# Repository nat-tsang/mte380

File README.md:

# Welcome to MTE380: PiDdy
We're a team of 5 students from the University of Waterloo tasked with creating a search and rescue robot to complete a course, via line following with computer vision, pick up a lego man and drop off the lego man in a safe zone. 

The course consists of a 6x6 grid of 30cm x 30cm squares, with a red tape path guiding the robot from the starting point to the target. A green tape box outlines two safe zones which the Lego man can be dropped off in. 

On game day, our robot was able to achieve times of 15 seconds on the first two runs, and 13 seconds in the third run. In total it weighed 131 g, mostly thanks to the mechanical and electrical design of the robot. The robot's software architecutre consisted of a Teensy MCU running the main control logic, and a Pixy camera module for the perception. 
# Software

This repo contains all of the software behind our robot, PiDdy. It specifically contains the PD controller for line following, the main state machine for feature arbitration between line following, picking up the lego man and dropping off the lego man.

## Code Standards

We are following OOP coding practices for clean, reusable code.

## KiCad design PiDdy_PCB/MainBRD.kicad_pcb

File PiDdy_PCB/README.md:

Space for all things to do custom pcb (PiDdy's chassis)

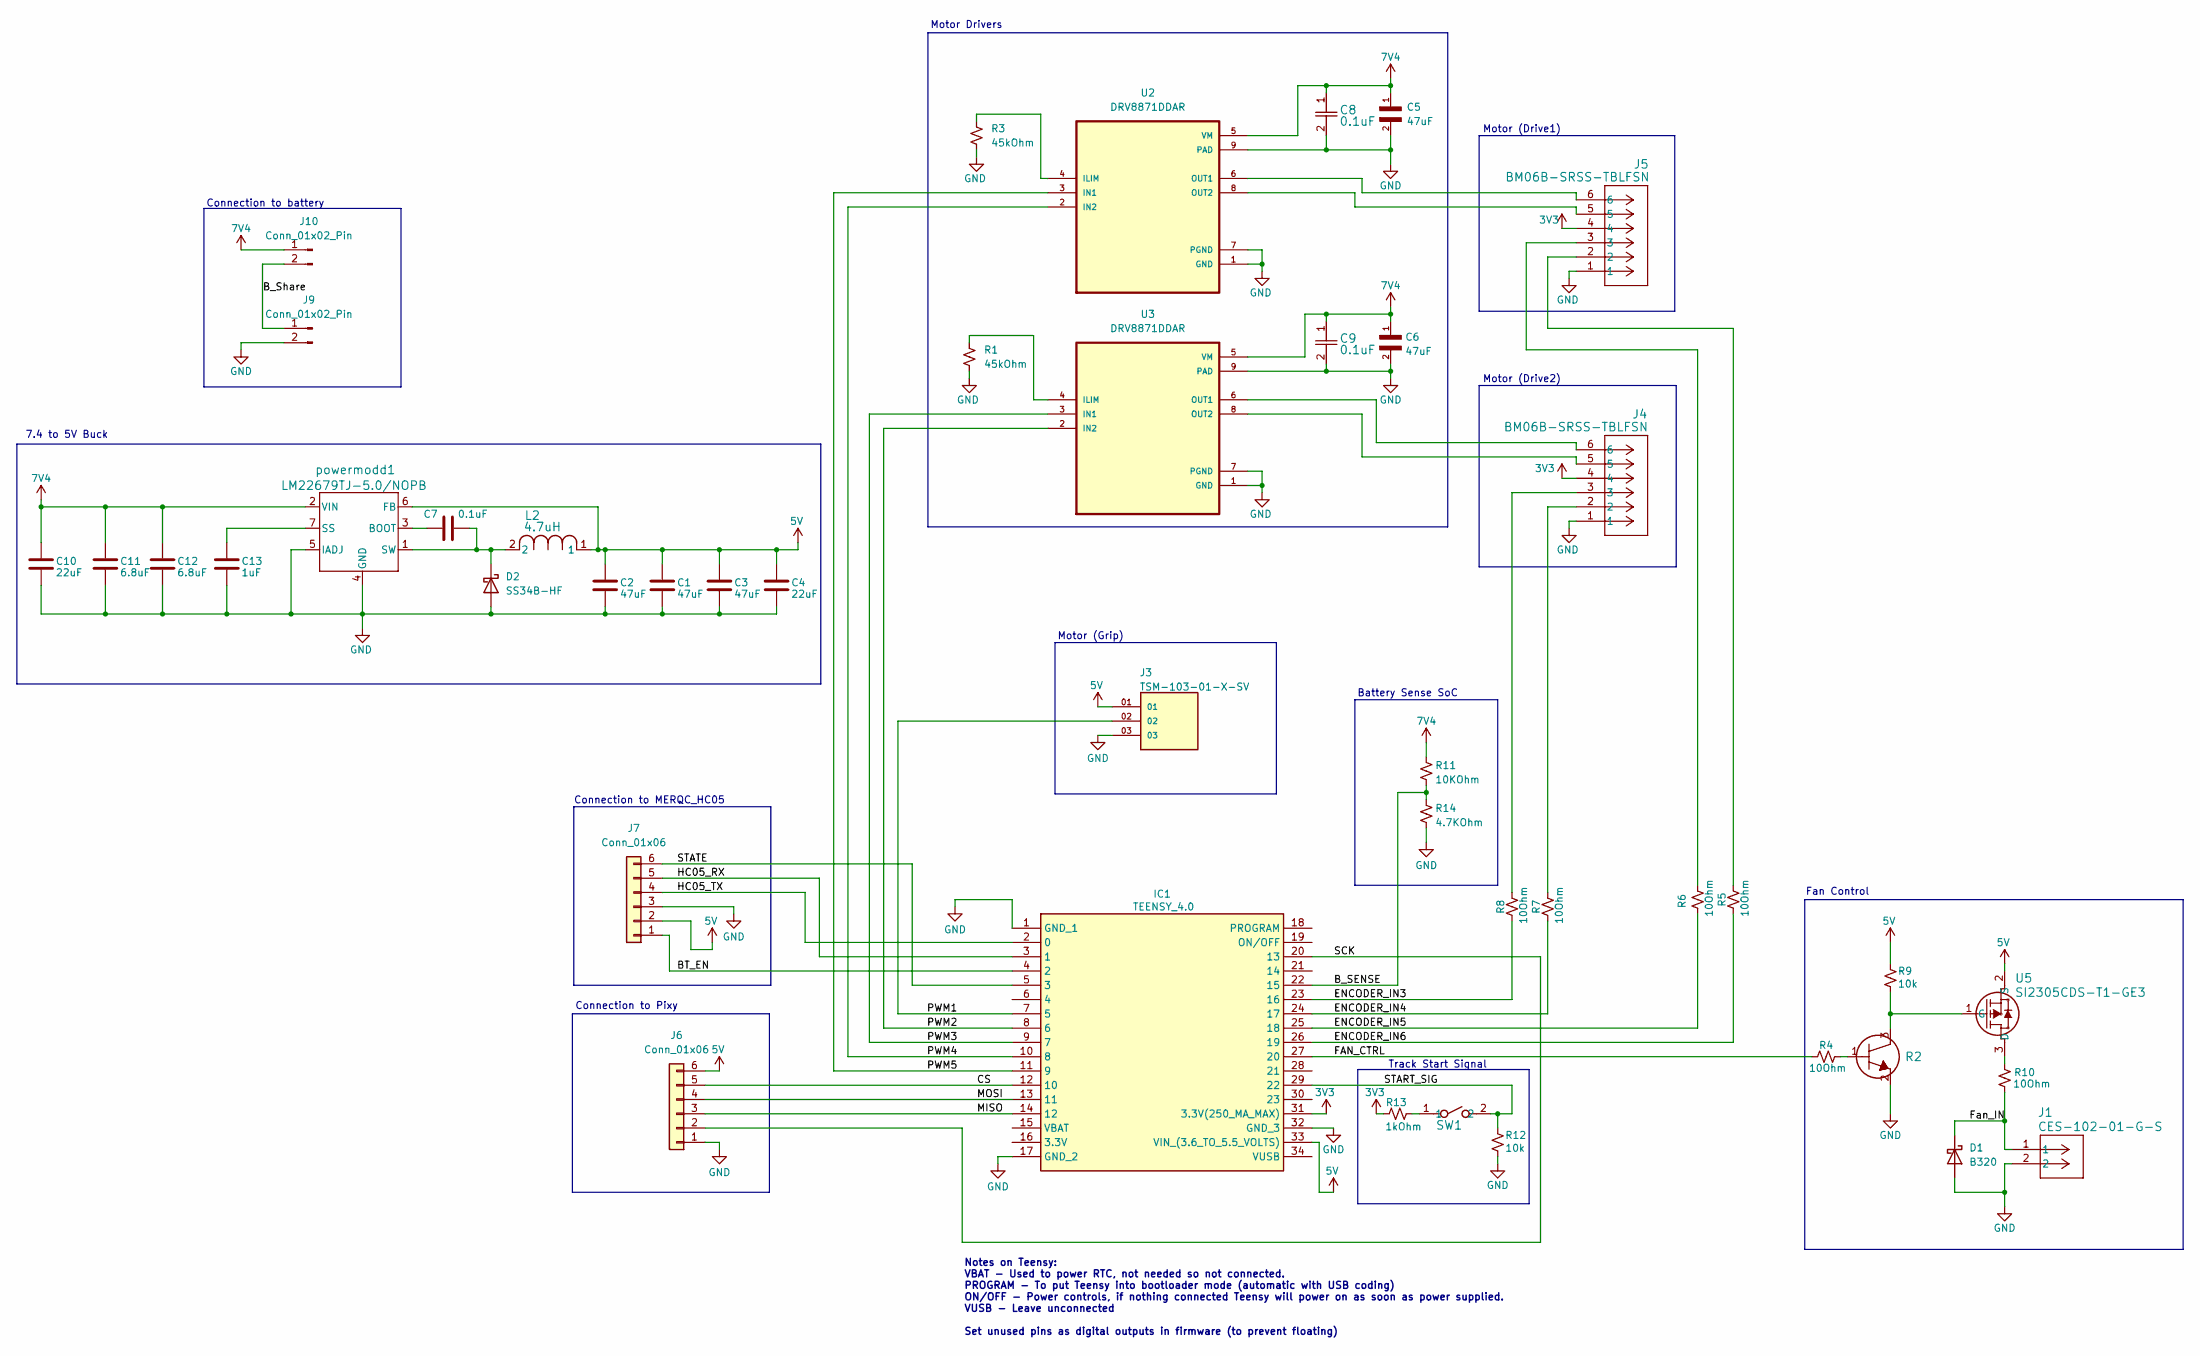
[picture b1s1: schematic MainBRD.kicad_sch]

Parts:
C1, C2, C3, C5, C6: 47uF; C_1210_3225Metric_Pad1.33x2.70mm_HandSolder
C4, C10: 22uF; C_1206_3216Metric_Pad1.33x1.80mm_HandSolder
C7: 0.1uF; C_0402_1005Metric_Pad0.74x0.62mm_HandSolder
C8, C9: 0.1uF; C_0402_1005Metric
C11: 6.8uF; LED_0805_2012Metric_Pad1.15x1.40mm_HandSolder
C12: 6.8uF; C_0805_2012Metric_Pad1.18x1.45mm_HandSolder
C13: 1uF; C_0402_1005Metric_Pad0.74x0.62mm_HandSolder
D1: B320; D_SMC
D2: SS34B-HF; SS34B
IC1: TEENSY_4.0; TEENSY40; Manufacturer_Part_Number TEENSY 4.0
J1: CES-102-01-G-S; CON2_1X2_TU_SLW_SAI
J3: TSM-103-01-X-SV; SAMTEC_TSM-103-01-X-SV; PARTREV D
J4, J5: BM06B-SRSS-TBLFSN; CONN_BM06B-SRSS-TB_JST
J6, J7: Conn_01x06; PinHeader_1x06_P2.54mm_Vertical
J9, J10: Conn_01x02_Pin; PinHeader_1x02_P2.54mm_Vertical
L2: 4.7uH; IND_VLS5045EX-4R7M
R1, R3: 45kOhm; RES_ERJ3EKF4532V
R2: 2SC5663T2L; TRANS_2SC5658T2_ROM
R4, R5, R6, R7, R8, R10: 10Ohm; ERJ_2RKF10R0X
R9, R12: 10k; RES_ERJ2RKF4702X
R11: 10KOhm; R_1206_3216Metric
R13: 1kOhm; ERJ_2RKF10R0X
R14: 4.7KOhm; R_1206_3216Metric
SW1: PTS636 SM50J SMTR LFS; SW_PTS636_CNK
U2, U3: DRV8871DDAR; lili_foot
U5: SI2305CDS-T1-GE3; TO-236_VIS
powermodd1: LM22679TJ-5.0/NOPB; LM22679TJ

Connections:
3V3: IC1.31 (3.3V(250_MA_MAX)), J4.4, J5.4, R13.2
5V: C1.1, C2.1, C3.1, C4.1, IC1.33 (VIN_(3.6_TO_5.5_VOLTS)), J3.01, J6.6, J7.2, L2.1, R9.1, U5.2 (S), powermodd1.6 (FB)
7V4: C5.1, C6.1, C8.1, C9.1, C10.1, C11.1, C12.1, J10.1, R11.1, U2.5 (VM), U3.5 (VM), powermodd1.2 (VIN)
/BT_EN: IC1.4 (2), J7.1
/B_SENSE: IC1.22 (15), R11.2, R14.1
/B_Share: J9.1, J10.2
/CS: IC1.12 (10), J6.5
/ENCODER_IN3: IC1.23 (16), R8.2
/ENCODER_IN4: IC1.24 (17), R7.2
/ENCODER_IN5: IC1.25 (18), R6.2
/ENCODER_IN6: IC1.26 (19), R5.2
/FAN_CTRL: IC1.27 (20), R4.2
/Fan_IN: D1.1 (K), J1.1, R10.2
/HC05_RX: IC1.3 (1), J7.5
/HC05_TX: IC1.2 (0), J7.4
/MISO: IC1.14 (12), J6.3
/MOSI: IC1.13 (11), J6.4
/PWM1: IC1.7 (5), J3.02
/PWM2: IC1.8 (6), U3.2 (IN2)
/PWM3: IC1.9 (7), U3.3 (IN1)
/PWM4: IC1.10 (8), U2.2 (IN2)
/PWM5: IC1.11 (9), U2.3 (IN1)
/SCK: IC1.20 (13), J6.2
/START_SIG: IC1.29 (22), R12.1, SW1.2
/STATE: IC1.5 (3), J7.6
GND: C1.2, C2.2, C3.2, C4.2, C5.2, C6.2, C8.2, C9.2, C10.2, C11.2, C12.2, C13.2, D1.2 (A), D2.2 (A), IC1.1 (GND_1), IC1.17 (GND_2), IC1.32 (GND_3), J1.2, J3.03, J4.1, J5.1, J6.1, J7.3, J9.2, R1.1, R2.2 (EMITTER), R3.1, R12.2, R14.2, U2.1 (GND), U2.7 (PGND), U2.9 (PAD), U3.1 (GND), U3.7 (PGND), U3.9 (PAD), powermodd1.4 (GND), powermodd1.5 (IADJ)
unnamed: C7.2, D2.1 (K), L2.2, powermodd1.1 (SW)
unnamed: J4.2, R7.1
unnamed: J4.3, R8.1
unnamed: J5.2, R5.1
unnamed: J5.3, R6.1
unnamed: R2.1 (Base), R4.1
unnamed: R2.3 (Collector), R9.2, U5.1 (G)
unnamed: R13.1, SW1.1
unnamed: R3.2, U2.4 (ILIM)
unnamed: J5.6, U2.6 (OUT1)
unnamed: J5.5, U2.8 (OUT2)
unnamed: R1.2, U3.4 (ILIM)
unnamed: J4.6, U3.6 (OUT1)
unnamed: J4.5, U3.8 (OUT2)
unnamed: R10.1, U5.3 (D)
unnamed: C7.1, powermodd1.3 (BOOT)
unnamed: C13.1, powermodd1.7 (SS)

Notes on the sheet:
Motor (Grip)
Motor (Drive1)
Connection to Pixy
Motor (Drive2)
Track Start Signal
Motor Drivers
Connection to battery
Notes on Teensy: VBAT - Used to power RTC, not needed so not connected. PROGRAM - To put Teensy into bootloader mode (automatic with USB coding) ON/OFF - Power controls, if nothing connected Teensy will power on as soon as power supplied. VUSB - Leave unconnected Set unused pins as digital outputs 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
Battery Sense SoC
Connection to MERQC_HC05
Fan Control
7.4 to 5V Buck

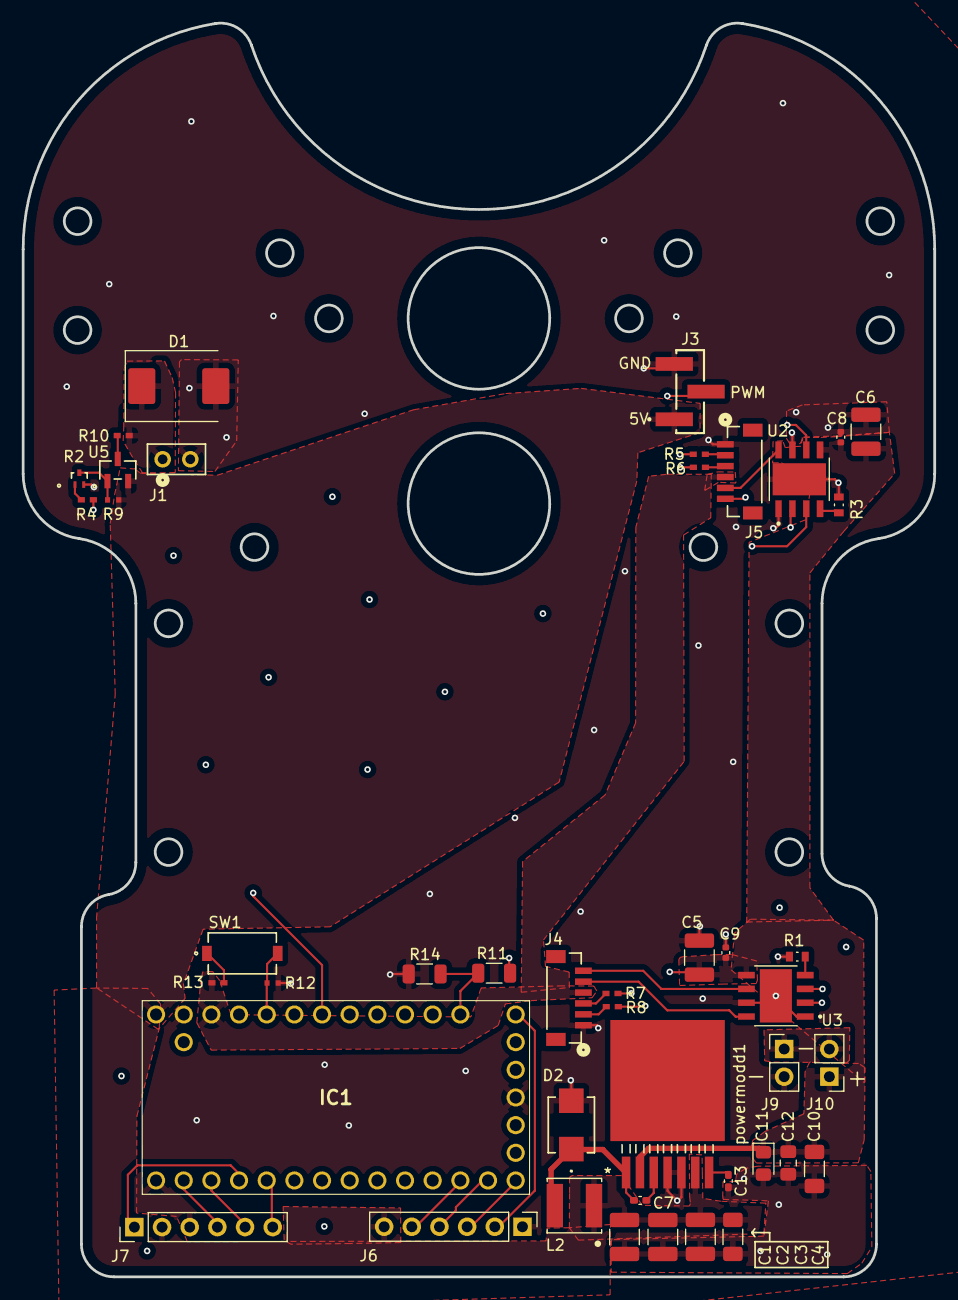
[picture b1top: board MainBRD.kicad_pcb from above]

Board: 4 copper layers, 83.7 x 115.1 mm, 44 parts (0 on the bottom side), 43 nets.

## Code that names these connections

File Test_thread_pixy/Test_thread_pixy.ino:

#include <TeensyThreads.h>
#include <Pixy2.h>

Pixy2 pixy;
// Motor + Board Parameters
const int LEFT_IN2 = 6;
const int LEFT_IN1 = 7;   // left wheel
const int RIGHT_IN2 = 8;  // right wheel
const int RIGHT_IN1 = 9;  // right wheel

const int ENCODER_IN3 = 16;  // Right
const int ENCODER_IN4 = 17;  // Right
const int ENCODER_IN5 = 18;  // Left
const int ENCODER_IN6 = 19;  // Left

const int FAN_CTRL = 20;
const int START_SIG = 22;  // Pin 22 is connected to button

const int SPEED = 80;

// Global Variables for State Transitions
volatile bool buttonPressed = false;
volatile bool greenDetected = false;
volatile bool goingOut = true;
volatile bool legoManCaptured = false;
volatile bool bullseyeDetected = false;

void setup() {
  Serial.begin(115200);
  while (!Serial);
  Serial.println("serial is starting");
  pinMode(LEFT_IN1, OUTPUT);
  pinMode(LEFT_IN2, OUTPUT);
  pinMode(RIGHT_IN1, OUTPUT);
  pinMode(RIGHT_IN2, OUTPUT);

  pinMode(START_SIG, INPUT_PULLDOWN);
  pinMode(FAN_CTRL, OUTPUT);
  pinMode(LED_BUILTIN, OUTPUT);
  digitalWrite(LED_BUILTIN, LOW);  //LED Off

  //Pixy Initialization
  pixy.init();
}

void controlThread() {
  while (true) {
    int buttonState = digitalRead(START_SIG);

    if (buttonState) {
      while (digitalRead(START_SIG)) {
        Serial.println("Button still pressed. Take finger off.");
      }

      if (bullseyeDetected && !legoManCaptured) {
        Serial.println("detected bullseye, finding lego man")
        legoManCaptured = findLegoMan(); //subroutine for collecting legoman, returns true
      }

      if (legoManCaptured && goingOut) {
        Serial.println("legoman captured, turning 180");
        execute180Turn();
        goingOut = false; // marks that PiDdy is no longer going there, now returning
        bullseyeDetected = false; // Reset
      }

      if (!goingOut && greenDetected) {
        Serial.println("detected green box, dropping off legoman");
        releaseLegoMan();
        greenDetected = false;
        legoManCaptured = false; 
      }
      threads.yield();
    }
  }
}

void lineTrackingThread() {
  pixy
  while (true) {
    if (!greenDetected && !bullseyeDetected) {
      
    }

    // Green box detected within specific threshold
    if (!goingOut && greenObjectDetected) {
      Serial.println("green object detected, switching to deposit lego man");
      delay(100);  // delay to prevent busy-waiting (this is where a cpu constantly checks a condition instead of running other important tasks)
      threads.yield();
    } else {
      pixy.line.getMainFeatures();
      Serial.println("tracking line...");
      delay(50);
      // Main Line tracking code (insert member functions from PD controller)
    }
  }
}

void colourClassification() {
  while (true) {
    pixy.ccc.getBlocks();

    for (int i = 0; i < pixy.ccc.numBlocks; i++) {
      // Pixy should only be trained on Lego Man colour (1) + green box (2)?
      if (pixy.ccc.blocks[i].signature == 2) {
        greenObjectDetected = true;
        Serial.println("green object detected, switching ")
      }
    }

    if (greenObjectDetected && !legoManDropped) {
      // enter dropping Lego man code then yield this thread to line tracking
    }
  }
}

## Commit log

2025-03-15 Initial add of script for Milestone 4
2025-03-17 Update with PD controller
2025-03-17 trial and error pixy threading
2025-03-17 Initial update for step graph
2025-03-18 Update with step input
2025-03-18 PID control edit
2025-03-18 Change PD to track middle of the vector
2025-03-18 PID control pins changes
2025-03-18 Added alternate code for line following with colour components
2025-03-18 Fixed colour api logic
2025-03-18 update of current pid control
2025-03-19 Adding working color connected component tracking
2025-03-19 Adding bullseye stop logic
2025-03-19 vector line control with PD
2025-03-20 wednesday updates
2025-03-20 Update for design spec gripper test
2025-03-20 edit file name for pid control line
2025-03-20 New line pid tuning file
2025-03-20 renamed color tuning PID_tuning_color
2025-03-21 Adding nick's test to git
2025-03-21 Testing velocity control in .h file
2025-03-21 new file structure
2025-03-22 Ignore .DS_Store
2025-03-22 Removed unnecessary header file
2025-03-22 removed unused folder
2025-03-22 first script to test encoders
2025-03-22 Updates for milestone 6
2025-03-22 Functions for controlling motors
2025-03-22 fixed braking
2025-03-23 Added helpers and SMA/EMA helper functions
2025-03-23 add error to main.cpp
2025-03-23 Set speed function fix
2025-03-23 add filter
2025-03-23 global vars update
2025-03-23 adding button
2025-03-23 Tested 180 turn
2025-03-23 added helper functions for bullseye
2025-03-23 adding turn to lego man adjustment test script
2025-03-24 Velocity control
2025-03-24 stashing current commits
2025-03-24 determine Kf constants
2025-03-24 changed pixy constructor
2025-03-24 fixed Kf bug
2025-03-24 Update for PiDdy control with only steering, and adding switch statements for state control
2025-03-24 removed unused global var
2025-03-25 update before i go gym
2025-03-25 Edits to make similar to arduino
2025-03-25 chelsea working changes
2025-03-25 Fixed button logic
2025-03-25 Revert to compute sma
2025-03-25 changes for chels
2025-03-25 add ema filter to pid tuning
2025-03-25 Back to platform io yay
2025-03-25 Changed pixy error type to float
2025-03-25 Adding update for straightline bullseye
2025-03-25 lego align error fixes
2025-03-25 testing lamp on/off
2025-03-26 add main to backup
2025-03-26 change lego y target
2025-03-26 what are we even doing?
2025-03-26 losing it
2025-03-26 loooosing it git
2025-03-26 lol 2 am
2025-03-26 bul
2025-03-26 Rewrote PixyLineTracker to only call getBlocks once per loop
2025-03-26 State machine and helpers tested with no get block
2025-03-26 Bluetooth first testing
2025-03-27 BT and voltage sensing
2025-03-27 new main...let's see
2025-03-27 Set to idel after low batteries
2025-03-27 hi hello
2025-03-27 removed unused code
2025-03-27 main bare bones
2025-03-27 Configuring alignment to shayla
2025-03-27 Align to lego
2025-03-27 adding timestamps
2025-03-27 slow speed on alignment
2025-03-28 Move in increments towards shay
2025-03-28 turn to shayla
2025-03-28 turn from button push
2025-03-28 adding bare bones and turn
2025-03-28 slaying the shayla pickup
2025-03-28 chelsea green line found
2025-03-28 Added motor parameters to findBulleye func
2025-03-28 Ran good
2025-03-28 working version at 6:22
2025-03-28 save
2025-03-29 push the pwm
2025-03-29 update for organization
2025-03-29 update for mech & elec file
2025-03-30 Final Game Day PCB Files
